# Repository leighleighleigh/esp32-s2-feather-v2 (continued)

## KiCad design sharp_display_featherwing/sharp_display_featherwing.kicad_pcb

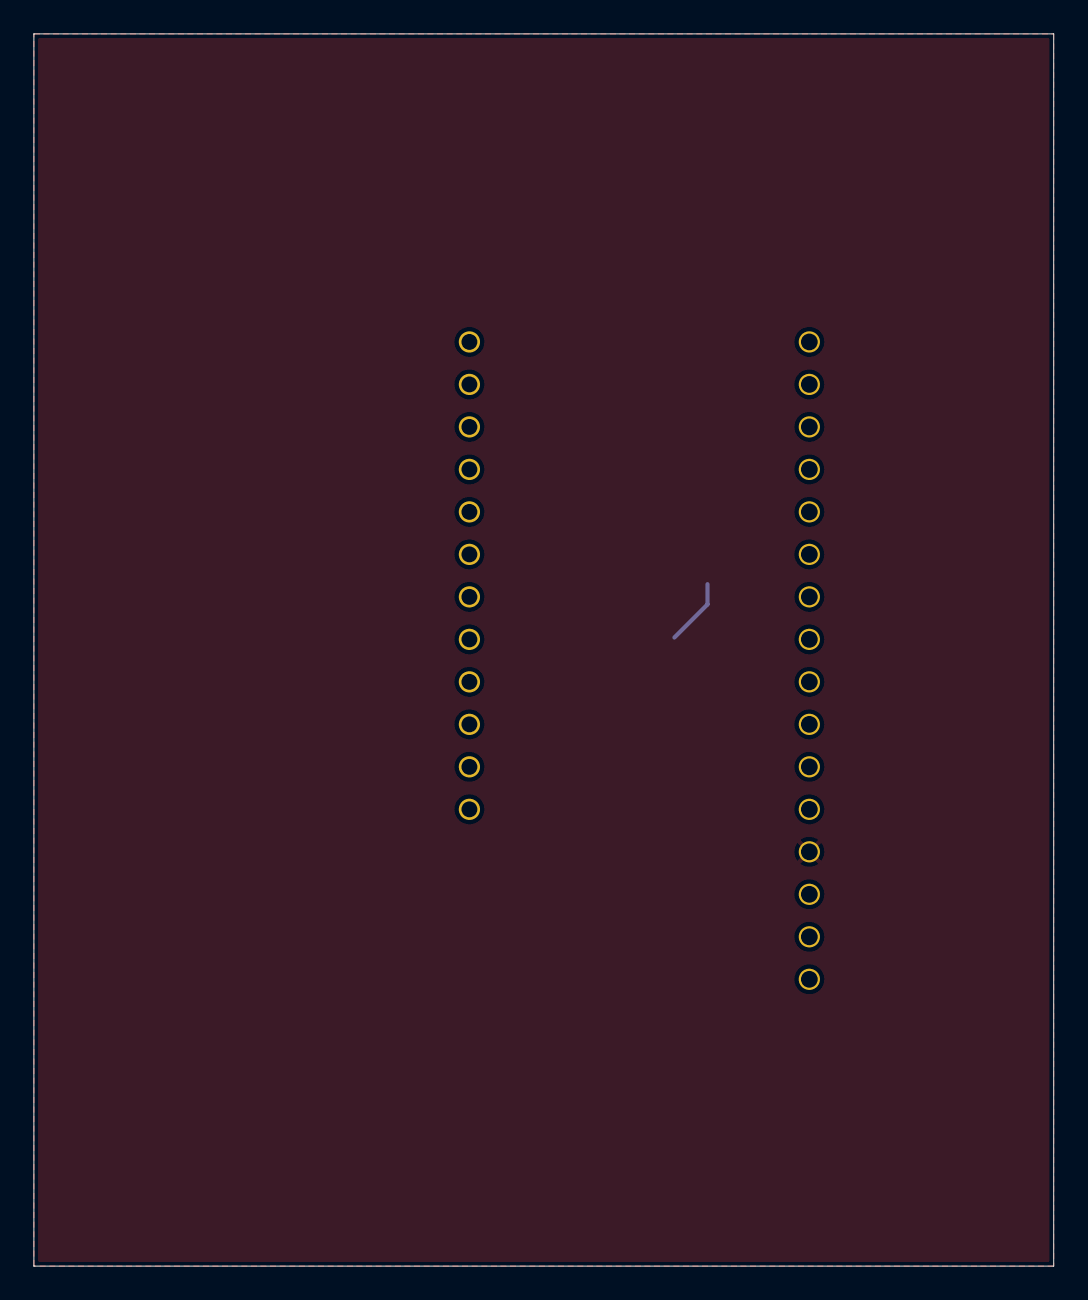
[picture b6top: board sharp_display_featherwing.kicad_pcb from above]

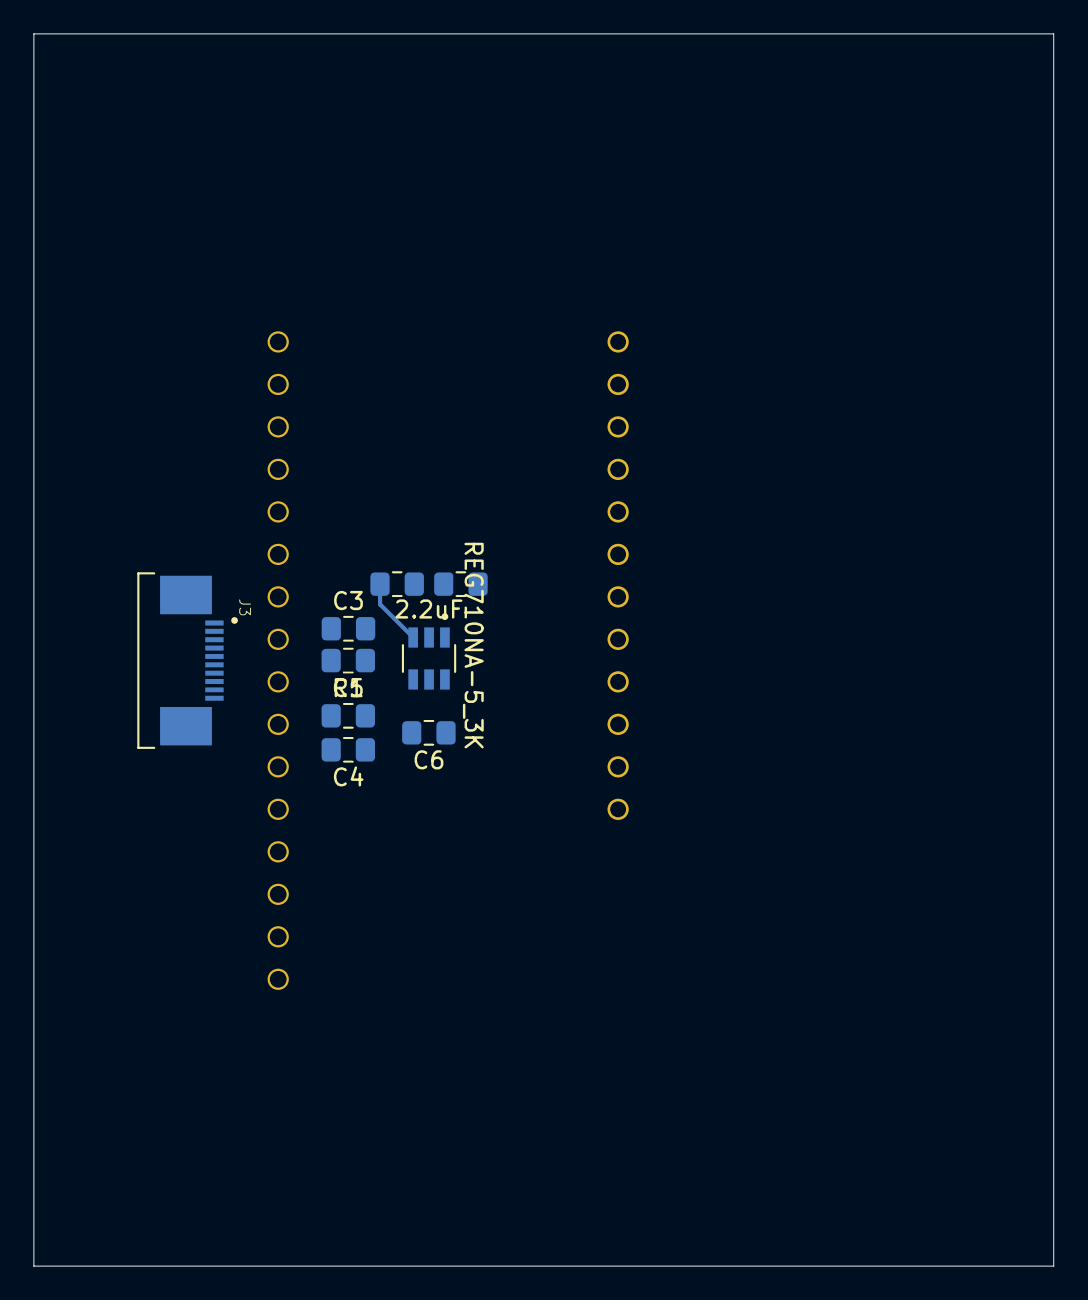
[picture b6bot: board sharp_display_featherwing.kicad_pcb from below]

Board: 2 copper layers, 61.0 x 73.7 mm, 11 parts (9 on the bottom side), 10 nets.

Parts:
C1, C2: 2.2uF; C_0805_2012Metric_Pad1.15x1.40mm_HandSolder
C3, C5: 0.1uF; C_0805_2012Metric_Pad1.15x1.40mm_HandSolder
C4: 1uF; C_0805_2012Metric_Pad1.15x1.40mm_HandSolder
C6: 220uF; C_0805_2012Metric_Pad1.15x1.40mm_HandSolder
J1: BOT; RoundPinHeader_1x16
J2: TOP; RoundPinHeader_1x12
J3: 1-1734592-0; TE_1-1734592-0
R1: 10k; R_0805_2012Metric_Pad1.15x1.40mm_HandSolder
U1: REG710NA-5_3K; SOT95P280X145-6N

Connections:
+3.3VA: C1.1, J1.1, U1.3 (ENABLE), U1.5 (VIN)
+5VD: C2.1, C4.1, C5.1, J3.6, J3.7, U1.1 (VOUT)
/DISP: C3.1, J3.5
/IO12: J1.12, J3.3
/SPI_SCK: J1.6, J3.1
/SPI_SDI: J1.4, J3.2
GND: C1.2, C2.2, C3.2, C4.2, C5.2, J1.13, J3.9, J3.10, J3.S1 (SHIELD), J3.S2 (SHIELD), R1.2, U1.2 (GND)
unnamed: J3.8, R1.1
unnamed: C6.2, U1.4 (CPUMP-)
unnamed: C6.1, U1.6 (CPUMP+)

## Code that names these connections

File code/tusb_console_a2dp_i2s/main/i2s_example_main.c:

/* I2S Example

    This example code will output 100Hz sine wave and triangle wave to 2-channel of I2S driver
    Every 5 seconds, it will change bits_per_sample [16, 24, 32] for i2s data

    This example code is in the Public Domain (or CC0 licensed, at your option.)

    Unless required by applicable law or agreed to in writing, this
    software is distributed on an "AS IS" BASIS, WITHOUT WARRANTIES OR
    CONDITIONS OF ANY KIND, either express or implied.
*/
#include <stdio.h>
#include "freertos/FreeRTOS.h"
#include "freertos/task.h"
#include "driver/i2s.h"
#include "driver/gpio.h"
#include "esp_system.h"
#include <math.h>

#include "esp_log.h"
#include "esp_vfs.h"

#include "tinyusb.h"
#include "tusb_cdc_acm.h"
#include "tusb_console.h"
#include "sdkconfig.h"
// #include "io_mux_reg.h"
#include "driver/gpio.h"


#define SAMPLE_RATE     (36000)
#define I2S_NUM         (0)
#define WAVE_FREQ_HZ    (100)
#define PI              (3.14159265)
#define I2S_BCK_IO      (GPIO_NUM_34)
#define I2S_WS_IO       (GPIO_NUM_33)
#define I2S_DO_IO       (GPIO_NUM_21)
#define I2S_DI_IO       (-1)
#define I2S_MUTE        (GPIO_NUM_7)

#define SAMPLE_PER_CYCLE (SAMPLE_RATE/WAVE_FREQ_HZ)

static const char *TAG = "example";

static void setup_triangle_sine_waves(int bits)
{
    int *samples_data = malloc(((bits+8)/16)*SAMPLE_PER_CYCLE*4);
    unsigned int i, sample_val;
    double sin_float, triangle_float, triangle_step = (double) pow(2, bits) / SAMPLE_PER_CYCLE;
    size_t i2s_bytes_write = 0;

    printf("\r\nTest bits=%d free mem=%d, written data=%d\n", bits, esp_get_free_heap_size(), ((bits+8)/16)*SAMPLE_PER_CYCLE*4);

    triangle_float = -(pow(2, bits)/2 - 1);

    for(i = 0; i < SAMPLE_PER_CYCLE; i++) {
        sin_float = sin(i * 2 * PI / SAMPLE_PER_CYCLE);
        if(sin_float >= 0)
            triangle_float += triangle_step;
        else
            triangle_float -= triangle_step;

        sin_float *= (pow(2, bits)/2 - 1);

        if (bits == 16) {
            sample_val = 0;
            sample_val += (short)triangle_float;
            sample_val = sample_val << 16;
            sample_val += (short) sin_float;
            samples_data[i] = sample_val;
        } else if (bits == 24) { //1-bytes unused
            samples_data[i*2] = ((int) triangle_float) << 8;
            samples_data[i*2 + 1] = ((int) sin_float) << 8;
        } else {
            samples_data[i*2] = ((int) triangle_float);
            samples_data[i*2 + 1] = ((int) sin_float);
        }

    }

    i2s_set_clk(I2S_NUM, SAMPLE_RATE, bits, 2);
    //Using push
    // for(i = 0; i < SAMPLE_PER_CYCLE; i++) {
    //     if (bits == 16)
    //         i2s_push_sample(0, &samples_data[i], 100);
    //     else
    //         i2s_push_sample(0, &samples_data[i*2], 100);
    // }
    // or write
    i2s_write(I2S_NUM, samples_data, ((bits+8)/16)*SAMPLE_PER_CYCLE*4, &i2s_bytes_write, 100);

    free(samples_data);
}

void app_main(void)
{
    /* Setting TinyUSB up */
    ESP_LOGI(TAG, "USB initialization");

    tinyusb_config_t tusb_cfg = { 0 }; // the configuration uses default values
    ESP_ERROR_CHECK(tinyusb_driver_install(&tusb_cfg));

    tinyusb_config_cdcacm_t amc_cfg = { 0 }; // the configuration uses default values
    ESP_ERROR_CHECK(tusb_cdc_acm_init(&amc_cfg));

    esp_tusb_init_console(TINYUSB_CDC_ACM_0); // log to usb
    ESP_LOGI(TAG, "USB initialization DONE");

    vTaskDelay(1000 / portTICK_PERIOD_MS);

    // setup mute pin
    gpio_config_t io_conf;
    //disable interrupt
    io_conf.intr_type = GPIO_INTR_DISABLE;
    //set as output mode
    io_conf.mode = GPIO_MODE_OUTPUT;
    //bit mask of the pins that you want to set,e.g.GPIO18/19
    io_conf.pin_bit_mask = (1ULL<<I2S_MUTE);
    //disable pull-down mode
    io_conf.pull_down_en = 0;
    //disable pull-up mode
    io_conf.pull_up_en = 1;
    //configure GPIO with the given settings
    gpio_config(&io_conf);

    gpio_set_level(I2S_MUTE,1);

    // Setup the MCLK pin
    // IO18 / U1RXD

    // WRITE_REG(IO_MUX_PIN_CTRL, 0x0);
    REG_WRITE(PIN_CTRL,0xFFFFF0F0);
    PIN_FUNC_SELECT(PERIPHS_IO_MUX_DAC_2_U, FUNC_DAC_2_CLK_OUT3);
    // PIN_FUNC_SELECT(PERIPHS_IO_MUX_U0TXD_U, FUNC_U0TXD_CLK_OUT3);
    // PIN_FUNC_SELECT(PERIPHS_IO_MUX_GPIO0_U, FUNC_GPIO0_CLK_OUT1);

    // Direct the clock out
    // PIN_CTRL[3:0] = 0x0;
    // PIN_CTRL[11:8] = 0x0;

    //for 36Khz sample rates, we create 100Hz sine wave, every cycle need 36000/100 = 360 samples (4-bytes or 8-bytes each sample)
    //depend on bits_per_sample
    //using 6 buffers, we need 60-samples per buffer
    //if 2-channels, 16-bit each channel, total buffer is 360*4 = 1440 bytes
    //if 2-channels, 24/32-bit each channel, total buffer is 360*8 = 2880 bytes
    i2s_config_t i2s_config = {
        .mode = I2S_MODE_MASTER | I2S_MODE_TX,                                  // Only TX
        .sample_rate = SAMPLE_RATE,
        .bits_per_sample = 16,
        .channel_format = I2S_CHANNEL_FMT_RIGHT_LEFT,                           //2-channels
        .communication_format = I2S_COMM_FORMAT_STAND_MSB,
        .dma_buf_count = 6,
        .dma_buf_len = 60,
        .use_apll = false,
        .intr_alloc_flags = ESP_INTR_FLAG_LEVEL1                                //Interrupt level 1
    };
    i2s_pin_config_t pin_config = {
        .bck_io_num = I2S_BCK_IO,
        .ws_io_num = I2S_WS_IO,
        .data_out_num = I2S_DO_IO,
        .data_in_num = I2S_DI_IO                                               //Not used
    };
    i2s_driver_install(I2S_NUM, &i2s_config, 0, NULL);
    i2s_set_pin(I2S_NUM, &pin_config);

    int test_bits = 16;
    while (1) {
        setup_triangle_sine_waves(test_bits);
        vTaskDelay(5000/portTICK_RATE_MS);
        test_bits += 8;
        if(test_bits > 32)
            test_bits = 16;

    }

}

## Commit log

2021-03-14 Initial commit.
2021-03-14 MCP2518 CAN Project started
2021-03-19 I2C experiments
2021-03-23 PWM Outputs babey
2021-03-27 Started work on BM83 featherwing.
2021-04-06 BM83 work
2021-04-28 BM83 SPST switch
2021-04-30 BM83 board first route. Needs labelling
2021-05-01 First gerber output for BM83
2021-05-01 BM83 rev 2 ordered.
2021-05-01 Fixed no power routed to DAC
2021-05-05 Added symbol and footprint for new codec
2021-05-09 BM83 uart thru esp32s2 not working yet
2021-05-09 Uhh, progress?
2021-05-22 Working example of some commands being sent to BM83 over uart
2021-05-22 Made message list better with delays
2021-05-30 Very good programming in action
2021-05-30 Added vscode task
2021-05-31 Working on proper UART pattern handling for RX. RAW TX implemented.
2021-05-31 Successful ACK decoding
2021-05-31 LE signalling events printed
2021-05-31 Todo note
2021-05-31 Uploading
2021-05-31 Dac featherwing schematic v2
2021-05-31 Work on DAC Featherwing v2
2021-06-01 Capacitors checked. TRRS pins checked. 3.5mm Footprint made. Performing layout and routing.
2021-06-02 PCB changed
2021-06-02 Full route #1 complete
2021-06-02 Stuff
2021-06-03 Minor updates to ground plane
2021-06-03 Removed REFs
2021-06-03 Redid routing to be much better
2021-06-03 DACV2 Complete. Ordered. Checked other files.
2021-06-04 Updated code to include DEEM and MUTE pins
2021-06-04 Random files
2021-06-05 Writing MCP2518 software
2021-06-05 Work on finding correct commands
2021-06-05 Gitignore updated to remove build folder
2021-06-05 Added build folder ignore to other projects
2021-06-05 Work on SPI format for MCP2518
2021-06-05 PINS AROUND THE WRONG WAY
2021-06-06 Update settings
2021-06-11 Simple i2c scanner back
2021-06-11 Getting new DAC to work
2021-06-23 Code for simple testing
2021-06-23 Decided on no deem
2021-06-23 Adjusted folder name
2021-06-23 Added register bit timings
2021-07-13 Removed old
2021-07-18 Working DACv2!
    Damn register default settings kicked me in the ass for a whole day, but I finally got it working.
    Now I need to make it more robust for changing audio sample rates and depths - and write a proper header file for it.
2021-07-18 Renamed
2021-07-18 Major cleanup
2021-07-18 Tweaked menuconfig to remove dependancy on TinyUSB. This allows for faster reflashing
2021-07-18 Battery formatting. Register tweaks.
2021-07-18 Tweaks
2021-07-20 Battery monitoring
